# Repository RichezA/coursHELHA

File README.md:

# This repo's role is to store and archive all the stuff i did during my studies at helha

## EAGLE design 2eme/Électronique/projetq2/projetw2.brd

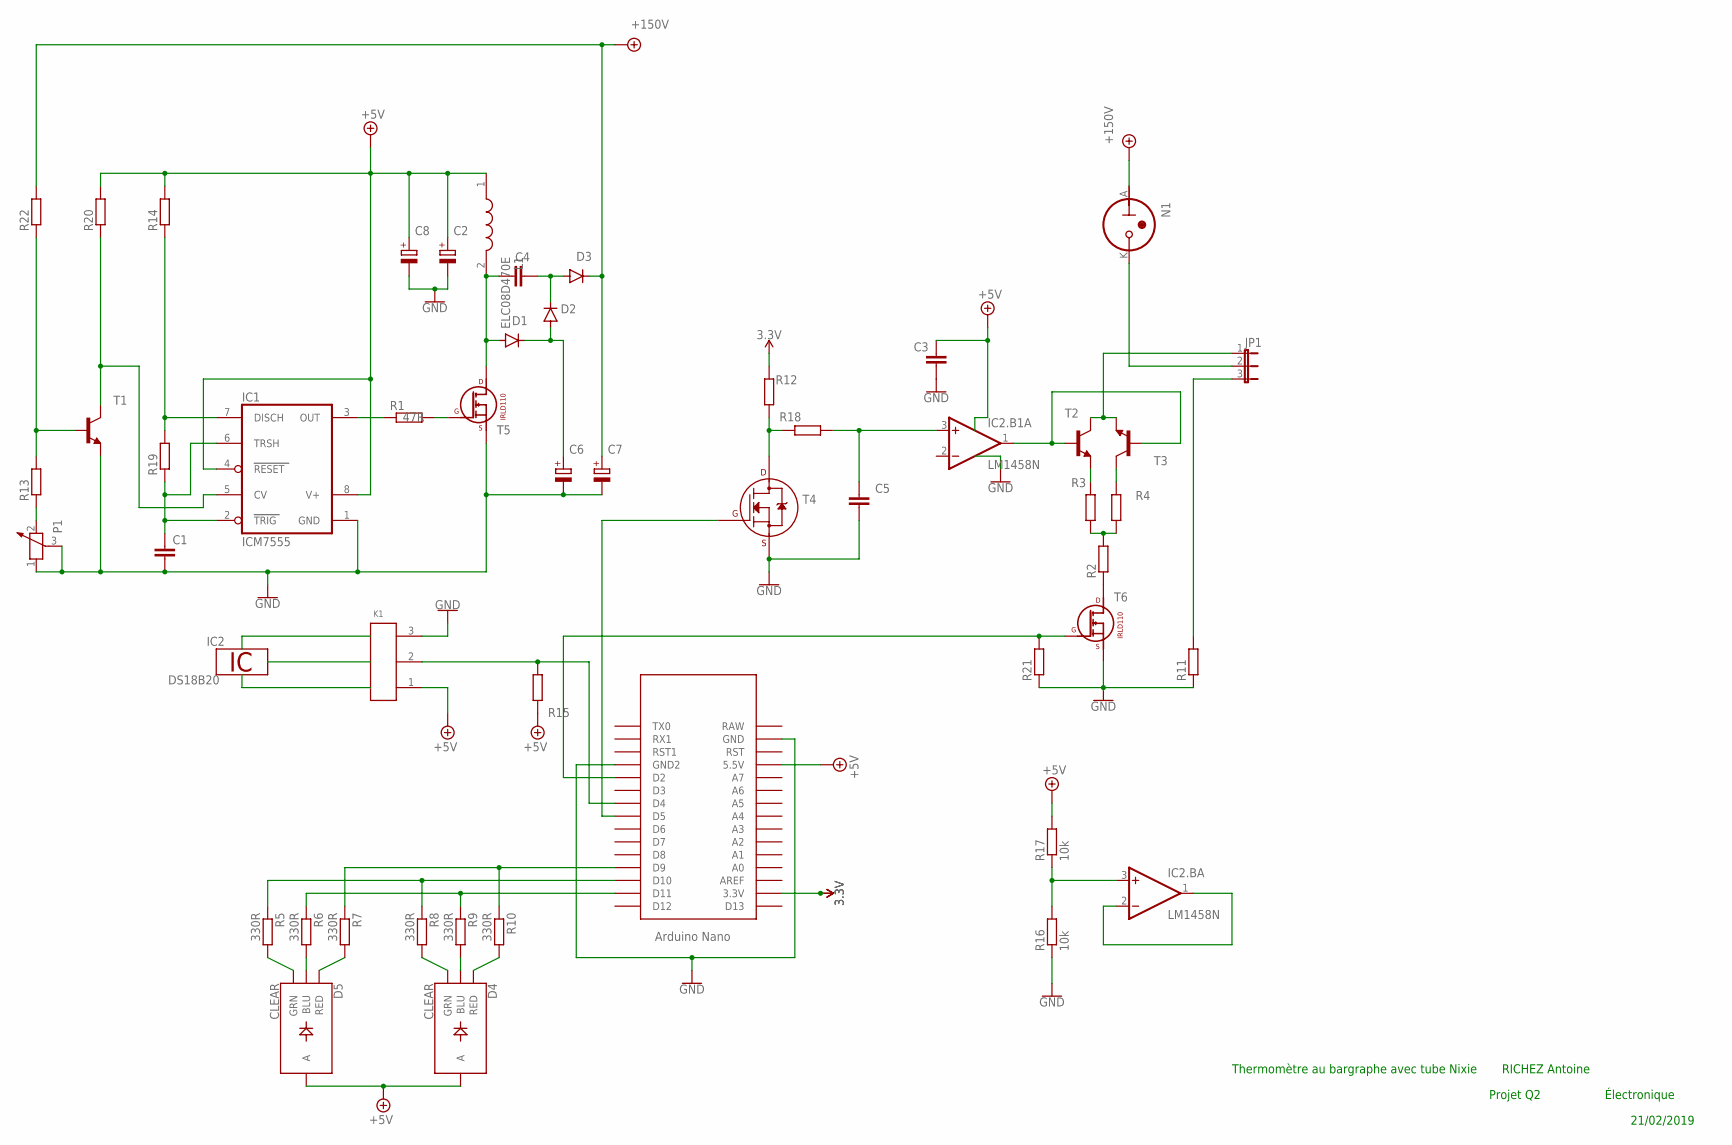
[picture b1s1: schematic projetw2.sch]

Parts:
C1: C-EU025-024X044; C025-024X044
C2, C6, C7, C8: CPOL-EUE2,5-6E; E2,5-6E
C3, C4, C5: C-EU025-030X050; C025-030X050
D1, D2, D3: MUR150RL; DO41-10
D4, D5: CLEAR; LED-RGB-THRU
IC1: ICM7555; DIL08
IC2: DS18B20; TO92-
IC2.B, IC2.B1: LM1458N; DIL08
JP1: JP2E; JP2
K1: 61900319521
L1: ELC08D470E; ELC08D
N1: IN-9
P1: POTENTIOMETER_PT-10; PT-10
R1: 47R; 0204/7
R2, R11, R15, R21: R-EU_0204/7; 0204/7
R3, R4, R12, R13, R14, R18, R19, R20, R22: R-EU_0207/2V; 0207/2V
R5, R6, R7, R8, R9, R10: 330R; 0204V
R16, R17: 10k; 0204V
T1: BC547B-NPN-TO92-CBE; TO92-CBE
T2, T3: MPSA42-NPN-TO92-EBC; TO92-EBC
T4: 2N7000_TO92; TO-92
T5, T6: -IRLD; IRLD110
U$1: NANO

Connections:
1W: IC2.2 (1W)
3.3V: R12.1, U$1.3.3V
+5V: C2.+, C3.1, C7.+, C8.+, D3.C, D4.2 (A), D5.2 (A), IC1.4 (RESET), IC1.8 (V+), K1.1 (3), L1.1, N1.A, R14.2, R15.1, R17.2, R20.2, R22.2, U$1.5V (5.5V)
GND: C1.2, C2.-, C3.2, C5.2, C6.-, C7.-, C8.-, IC1.1 (GND), IC2.1 (GND), K1.3 (1), P1.1, P1.3, R11.1, R16.1, R21.1, T1.E, T4.1 (S), T5.SOURCE, T6.SOURCE, U$1.GND, U$1.GND1 (GND2)
unnamed: IC2.B.1 (OUT), IC2.B.2 (-IN)
unnamed: IC2.B.3 (+IN), R16.2, R17.1
unnamed: R7.1, R10.1, U$1.D9
unnamed: R5.1, R8.1, U$1.D10
unnamed: R6.1, R9.1, U$1.D11
unnamed: C1.1, IC1.2 (TRIG), IC1.6 (TRSH), R19.1
unnamed: D5.1 (RED), R7.2
unnamed: IC1.3 (OUT), R1.1
unnamed: R1.2, T5.GATE
unnamed: C4.1, D1.A, L1.2, T5.DRAIN1 (DRAIN)
unnamed: C6.+, D1.C, D2.A
unnamed: C4.2, D2.C, D3.A
unnamed: K1.2, R15.2, U$1.D4
unnamed: IC1.7 (DISCH), R14.1, R19.2
unnamed: D5.4 (BLU), R6.2
unnamed: D5.3 (GRN), R5.2
unnamed: D4.1 (RED), R10.2
unnamed: D4.4 (BLU), R9.2
unnamed: D4.3 (GRN), R8.2
unnamed: IC1.5 (CV), R20.1, T1.C
unnamed: R13.2, R22.1, T1.B
unnamed: P1.2, R13.1
unnamed: T4.2 (G), U$1.D5
unnamed: C5.1, IC2.B1.3 (+IN), R18.1
unnamed: R12.2, R18.2, T4.3 (D)
unnamed: R3.1, T2.E
unnamed: R4.1, T3.C
unnamed: R2.2, R3.2, R4.2
unnamed: R2.1, T6.DRAIN1 (DRAIN)
unnamed: IC2.B1.1 (OUT), T2.B, T3.B
unnamed: R21.2, T6.GATE, U$1.D2
unnamed: JP1.2, N1.K
unnamed: JP1.1, T2.C, T3.E
unnamed: JP1.3, R11.2
V+: IC2.B.8 (V+), IC2.B1.8 (V+)
V-: IC2.B.4 (V-), IC2.B1.4 (V-)
VDD: IC2.3 (VDD)

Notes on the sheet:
RICHEZ Antoine
Projet Q2
Thermomètre au bargraphe avec tube Nixie
Électronique
21/02/2019

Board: 2 copper layers, 51 parts (0 on the bottom side), 39 nets, no tracks yet.

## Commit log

2018-12-19 networking ccna2 exam ready
2018-12-24 added elec
2019-01-06 added advanced networking
2019-01-21 Added tce exam
2019-01-21 added tce mct
2019-02-21 added secondQ project
2019-03-01 added netwokring + electrical lesson
2019-05-10 electronic project added
2019-05-12 english file
2019-05-12 english is coming
2019-05-13 finished english folder'
2019-08-27 Cleared the directory
2019-10-09 added 3rd year folder + some courses
2019-10-10 added the weekly course of OS
2019-10-22 prod & OS lessons added
2019-10-25 added the seminaire + os course of the week
2019-11-28 added eveyrhting
2019-11-28 added OS course of the day
2019-12-05 added os course
2019-12-26 added os course + seminaires'
2020-01-07 added the debian exam synthesis
2024-07-12 Update gitattributes to support LFS
2024-07-12 Add 1st year courses

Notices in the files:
parts and their libraries:
Wire-to-Board: Copyright: Würth Elektronik
SparkFun-LED: Licensing: Creative Commons ShareAlike 4.0 International - https://creativecommons.org/licenses/by-sa/4.0
